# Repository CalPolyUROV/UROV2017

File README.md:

# UROV2017
The Git repository for UROV's 2016-2017 build year.

For the start of the year, everybody make their own folders for trying out sensor drivers. After you get your driver working, you can try your hand at adding it to the “main” program. Good luck!

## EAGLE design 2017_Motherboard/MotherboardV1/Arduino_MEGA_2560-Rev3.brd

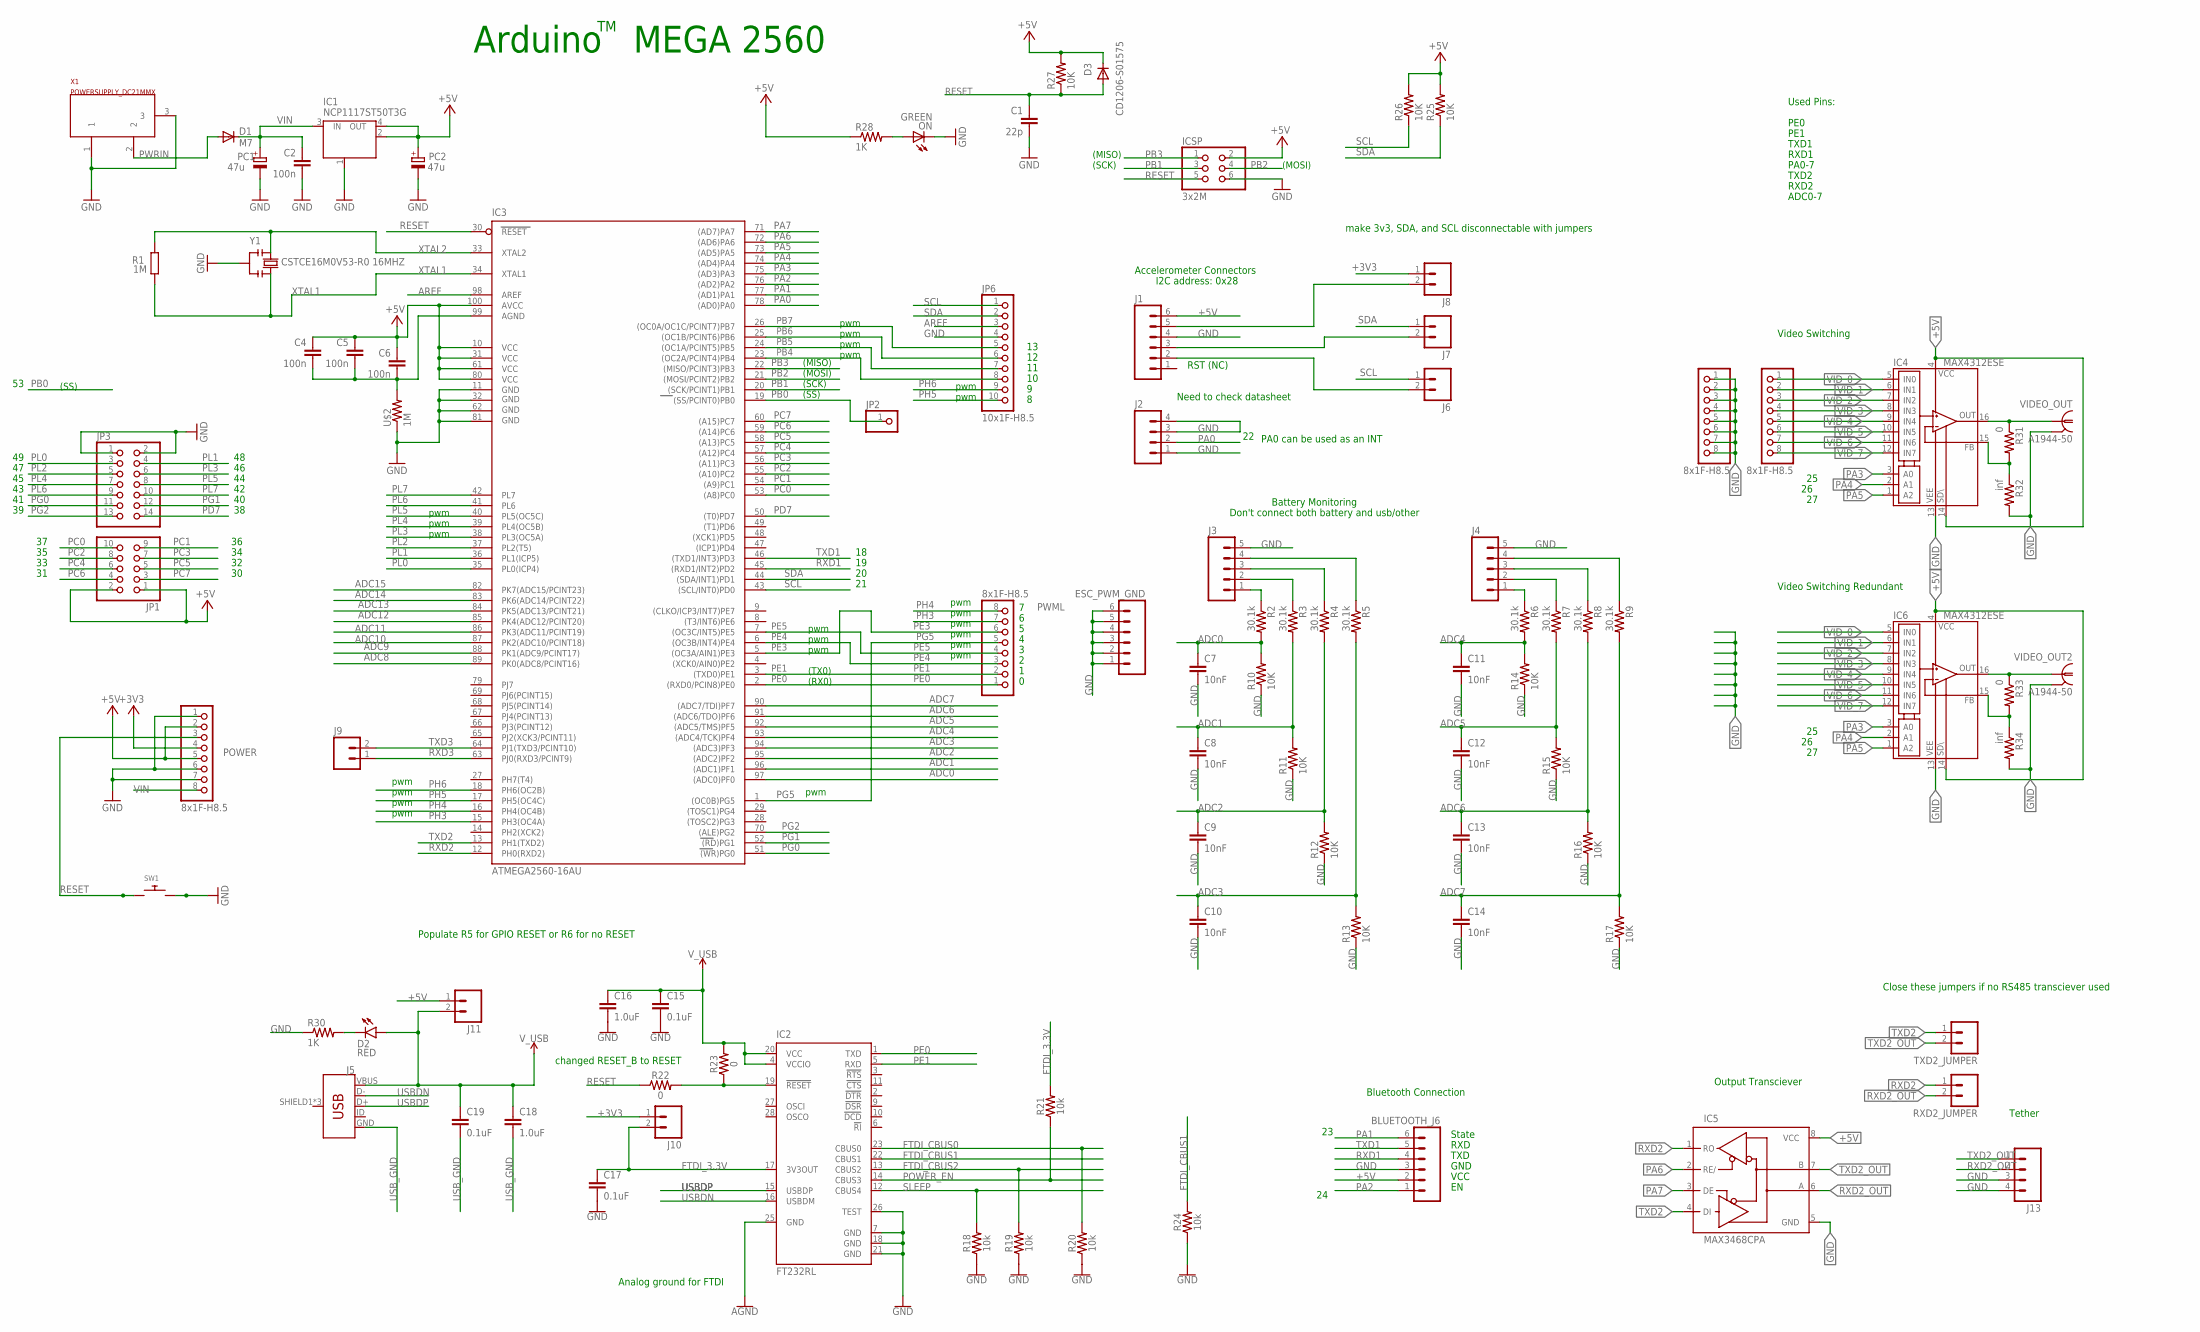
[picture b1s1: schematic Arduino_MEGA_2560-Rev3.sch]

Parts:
BLUETOOTH_J6: M06LONGPADS; 1X06_LONGPADS
C1: 22p; C0603-ROUND
C2, C4, C5, C6: 100n; C0603-ROUND
C7, C8, C9, C10, C11, C12, C13, C14: 10nF; 0603-CAP
C15, C17, C19: 0.1uF; 0603
C16, C18: 1.0uF; 0603
D1: M7; SMB
D2: RED; LED-0603
D3: CD1206-S01575; MINIMELF
ESC_PWM_GND: M06LONGPADS; 1X06_LONGPADS
IC1: NCP1117ST50T3G; SOT223
IC2: FT232RL; SSOP28
IC3: ATMEGA2560-16AU; TQFP100
IC4, IC6: MAX4312ESE; SO16
IC5: MAX3468CPA; DIL08
ICSP: 3x2M; 2X03
J1: M06LONGPADS; 1X06_LONGPADS
J2, J13: M04LONGPADS; 1X04_LONGPADS
J3, J4: M05JST-VERT; JST-5-PTH-VERT
J5: USB_MICRO-B_FEMALE-SMT; USB-B-MICRO-SMD
J6, J7, J8, J9, J10, J11: M02PTH; 1X02
JP1: PINHD-2X5; 2X05
JP2: PINHD-1X1; 1X01
JP3: PINHD-2X7; 2X07
JP6: 10x1F-H8.5; 1X10
ON: GREEN; CHIP-LED0805
PC1, PC2: 47u; PANASONIC_D
POWER: 8x1F-H8.5; 1X08
PWML: 8x1F-H8.5; 1X08
R1: 1M; R0603-ROUND
R2, R3, R4, R5, R6, R7, R8, R9: 30.1k; 0603-RES
R10, R11, R12, R13, R14, R15, R16, R17, R25, R26, R27: 10K; 0603-RES
R18, R19, R20, R21, R24: 10k; 0603
R22, R23: 0; 0603
R28, R30: 1K; 0603-RES
R31, R33: 0; 0603-RES
R32, R34: inf; 0603-RES
RXD2_JUMPER: M02PTH; 1X02
SW1: SWITCH_PUSHBUTTONC&K_KSS; BTN_CK_KSS
TXD2_JUMPER: M02PTH; 1X02
U$2: 1M; 0603-RES
VIDEO_IN: 8x1F-H8.5; 1X08
VIDEO_IN_GND: 8x1F-H8.5; 1X08
VIDEO_OUT, VIDEO_OUT2: A1944-50; A1944
X1: POWERSUPPLY_DC21MMX; POWERSUPPLY_DC-21MM
Y1: CSTCE16M0V53-R0 16MHZ; RESONATOR

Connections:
+3V3: J8.1, J10.1, POWER.4
+5V: BLUETOOTH_J6.2, C4.1, C5.1, C6.1, D3.C, IC1.2 (OUT), IC1.4 (OUT), IC3.10 (VCC), IC3.31 (VCC1), IC3.61 (VCC2), IC3.80 (VCC3), IC3.100 (AVCC), IC4.4 (V+), IC4.14 (!SHDN), IC5.8 (VCC), IC6.4 (V+), IC6.14 (!SHDN), ICSP.2, J1.6, J11.1, JP1.1, JP1.2, PC2.+, POWER.2, POWER.5, R25.2, R26.2, R27.2, R28.1
ADC0: C7.1, IC3.97 ((ADC0)PF0), R2.2, R10.2
ADC1: C8.1, IC3.96 ((ADC1)PF1), R3.2, R11.2
ADC2: C9.1, IC3.95 ((ADC2)PF2), R4.2, R12.2
ADC3: C10.1, IC3.94 ((ADC3)PF3), R5.2, R13.2
ADC4: C11.1, IC3.93 ((ADC4/TCK)PF4), R6.2, R14.2
ADC5: C12.1, IC3.92 ((ADC5/TMS)PF5), R7.2, R15.2
ADC6: C13.1, IC3.91 ((ADC6/TDO)PF6), R8.2, R16.2
ADC7: C14.1, IC3.90 ((ADC7/TDI)PF7), R9.2, R17.2
ADC8: IC3.89 (PK0(ADC8/PCINT16))
ADC9: IC3.88 (PK1(ADC9/PCINT17))
ADC10: IC3.87 (PK2(ADC10/PCINT18))
ADC11: IC3.86 (PK3(ADC11/PCINT19))
ADC12: IC3.85 (PK4(ADC12/PCINT20))
ADC13: IC3.84 (PK5(ADC13/PCINT21))
ADC14: IC3.83 (PK6(ADC14/PCINT22))
ADC15: IC3.82 (PK7(ADC15/PCINT23))
AGND: C4.2, C5.2, C6.2, IC2.25 (GND), IC3.99 (AGND), U$2.2
AREF: IC3.98 (AREF), JP6.3
FTDI_3.3V: C17.1, IC2.17 (3V3OUT), J10.2, R21.2
FTDI_CBUS0: IC2.23 (CBUS0), R20.2
FTDI_CBUS1: IC2.22 (CBUS1), R24.2
FTDI_CBUS2: IC2.13 (CBUS2), R19.2
GND: BLUETOOTH_J6.3, C1.2, C2.2, C7.2, C8.2, C9.2, C10.2, C11.2, C12.2, C13.2, C14.2, C15.2, C16.2, C17.2, ESC_PWM_GND.1, ESC_PWM_GND.2, ESC_PWM_GND.3, ESC_PWM_GND.4, ESC_PWM_GND.5, ESC_PWM_GND.6, IC1.1 (GND/ADJ), IC2.7 (GND), IC2.18 (GND), IC2.21 (GND), IC2.26 (TEST), IC3.11 (GND), IC3.32 (GND1), IC3.62 (GND2), IC3.81 (GND3), IC4.13 (V-), IC5.5 (GND), IC6.13 (V-), ICSP.6, J1.4, J2.1, J2.3, J2.4, J3.5, J4.5, J13.3, J13.4, JP3.1, JP3.2, JP6.4, ON.C, PC1.-, PC2.-, POWER.1, POWER.6, POWER.7, R10.1, R11.1, R12.1, R13.1, R14.1, R15.1, R16.1, R17.1, R18.1, R19.1, R20.1, R24.1, R30.1, R32.2, R34.2, SW1.P$2, U$2.1, VIDEO_IN_GND.1, VIDEO_IN_GND.2, VIDEO_IN_GND.3, VIDEO_IN_GND.4, VIDEO_IN_GND.5, VIDEO_IN_GND.6, VIDEO_IN_GND.7, VIDEO_IN_GND.8, VIDEO_OUT.2, VIDEO_OUT.3 (2), VIDEO_OUT.4 (2), VIDEO_OUT.5 (2), VIDEO_OUT2.2, VIDEO_OUT2.3 (2), VIDEO_OUT2.4 (2), VIDEO_OUT2.5 (2), X1.1, X1.3, Y1.2
unnamed: J3.1, R2.1
unnamed: ON.A, R28.2
unnamed: IC2.19 (!RESET), R22.2, R23.1
unnamed: J4.1, R6.1
unnamed: J3.2, R3.1
unnamed: J1.5, J8.2
unnamed: J3.3, R4.1
unnamed: J1.3, J7.2
unnamed: J3.4, R5.1
unnamed: J1.2, J6.2
unnamed: J4.2, R7.1
unnamed: J4.3, R8.1
unnamed: J4.4, R9.1
unnamed: D2.C, R30.2
unnamed: IC4.15 (FB), R31.2, R32.1
unnamed: IC6.15 (FB), R33.2, R34.1
PA0: IC3.78 ((AD0)PA0), J2.2
PA1: BLUETOOTH_J6.6, IC3.77 ((AD1)PA1)
PA2: BLUETOOTH_J6.1, IC3.76 ((AD2)PA2)
PA3: IC3.75 ((AD3)PA3), IC4.3 (A0), IC6.3 (A0)
PA4: IC3.74 ((AD4)PA4), IC4.2 (A1), IC6.2 (A1)
PA5: IC3.73 ((AD5)PA5), IC4.1 (A2), IC6.1 (A2)
PA6: IC3.72 ((AD6)PA6), IC5.2 (RE/)
PA7: IC3.71 ((AD7)PA7), IC5.3 (DE)
PB0: IC3.19 ((SS/PCINT0)PB0), JP2.1
PB1: IC3.20 ((SCK/PCINT1)PB1), ICSP.3
PB2: IC3.21 ((MOSI/PCINT2)PB2), ICSP.4
PB3: IC3.22 ((MISO/PCINT3)PB3), ICSP.1
PB4: IC3.23 ((OC2A/PCINT4)PB4), JP6.8
PB5: IC3.24 ((OC1A/PCINT5)PB5), JP6.7
PB6: IC3.25 ((OC1B/PCINT6)PB6), JP6.6
PB7: IC3.26 ((OC0A/OC1C/PCINT7)PB7), JP6.5
PC0: IC3.53 ((A8)PC0), JP1.10
PC1: IC3.54 ((A9)PC1), JP1.9
PC2: IC3.55 ((A10)PC2), JP1.8
PC3: IC3.56 ((A11)PC3), JP1.7
PC4: IC3.57 ((A12)PC4), JP1.6
PC5: IC3.58 ((A13)PC5), JP1.5
PC6: IC3.59 ((A14)PC6), JP1.4
PC7: IC3.60 ((A15)PC7), JP1.3
PD7: IC3.50 ((T0)PD7), JP3.14
PE0: IC2.1 (TXD), IC3.2 ((RXD0/PCIN8)PE0), PWML.1
PE1: IC2.5 (RXD), IC3.3 ((TXD0)PE1), PWML.2
PE3: IC3.5 ((OC3A/AIN1)PE3), PWML.6
PE4: IC3.6 ((OC3B/INT4)PE4), PWML.3
PE5: IC3.7 ((OC3C/INT5)PE5), PWML.4
PG0: IC3.51 ((WR)PG0), JP3.11
PG1: IC3.52 ((RD)PG1), JP3.12
PG2: IC3.70 ((ALE)PG2), JP3.13
PG5: IC3.1 ((OC0B)PG5), PWML.5
PH3: IC3.15 (PH3(OC4A)), PWML.7
PH4: IC3.16 (PH4(OC4B)), PWML.8
PH5: IC3.17 (PH5(OC4C)), JP6.10
PH6: IC3.18 (PH6(OC2B)), JP6.9
PL0: IC3.35 (PL0(ICP4)), JP3.3
PL1: IC3.36 (PL1(ICP5)), JP3.4
PL2: IC3.37 (PL2(T5)), JP3.5
PL3: IC3.38 (PL3(OC5A)), JP3.6
PL4: IC3.39 (PL4(OC5B)), JP3.7
PL5: IC3.40 (PL5(OC5C)), JP3.8
PL6: IC3.41 (PL6), JP3.9
PL7: IC3.42 (PL7), JP3.10
POWER_EN: IC2.14 (CBUS3), R21.1
PWRIN: D1.A, X1.2
RESET: C1.1, D3.A, IC3.30 (RESET), ICSP.5, POWER.3, R22.1, R27.1, SW1.P$1
RXD1: BLUETOOTH_J6.4, IC3.45 ((RXD1/INT2)PD2)
RXD2: IC3.12 (PH0(RXD2)), IC5.1 (RO), RXD2_JUMPER.1
RXD2_OUT: IC5.6 (A), J13.2, RXD2_JUMPER.2
RXD3: IC3.63 (PJ0(RXD3/PCINT9)), J9.1
SCL: IC3.43 ((SCL/INT0)PD0), J6.1, JP6.1, R26.1
SDA: IC3.44 ((SDA/INT1)PD1), J7.1, JP6.2, R25.1
SLEEP: IC2.12 (CBUS4), R18.2
TXD1: BLUETOOTH_J6.5, IC3.46 ((TXD1/INT3)PD3)
TXD2: IC3.13 (PH1(TXD2)), IC5.4 (DI), TXD2_JUMPER.1
TXD2_OUT: IC5.7 (B), J13.1, TXD2_JUMPER.2
TXD3: IC3.64 (PJ1(TXD3/PCINT10)), J9.2
USBDN: IC2.16 (USBDM), J5.D-
USBDP: IC2.15 (USBDP), J5.D+
USB_GND: C18.2, C19.2, J5.GND
VIDEO_OUT: IC4.16 (OUT), R31.1, VIDEO_OUT.1
VIDEO_OUT1: IC6.16 (OUT), R33.1, VIDEO_OUT2.1
VID_0: IC4.5 (IN0), IC6.5 (IN0), VIDEO_IN.1
VID_1: IC4.6 (IN1), IC6.6 (IN1), VIDEO_IN.2
VID_2: IC4.7 (IN2), IC6.7 (IN2), VIDEO_IN.3
VID_3: IC4.8 (IN3), IC6.8 (IN3), VIDEO_IN.4
VID_4: IC4.9 (IN4), IC6.9 (IN4), VIDEO_IN.5
VID_5: IC4.10 (IN5), IC6.10 (IN5), VIDEO_IN.6
VID_6: IC4.11 (IN6), IC6.11 (IN6), VIDEO_IN.7
VID_7: IC4.12 (IN7), IC6.12 (IN7), VIDEO_IN.8
VIN: C2.1, D1.C, IC1.3 (IN), PC1.+, POWER.8
V_USB: C15.1, C16.1, C18.1, C19.1, D2.A, IC2.4 (VCCIO), IC2.20 (VCC), J5.VBUS, J11.2, R23.2
XTAL1: IC3.34 (XTAL1), R1.1, Y1.3
XTAL2: IC3.33 (XTAL2), R1.2, Y1.1

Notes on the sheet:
Arduino MEGA 2560
(SCK)
(MISO)
(MOSI)
pwm
(TX0)
(RX0)
(SS)
Accelerometer Connectors
Battery Monitoring
Need to check datasheet
Don't connect both battery and usb/other
Populate R5 for GPIO RESET or R6 for no RESET
Analog ground for FTDI
make 3v3, SDA, and SCL disconnectable with jumpers
RST (NC)
PA0 can be used as an INT
I2C address: 0x28
Bluetooth Connection
State
RXD
TXD
GND
VCC
Used Pins:
PE0
PE1
TXD1
RXD1
PA0-7
ADC0-7
Tether
Video Switching
Output Transciever
Close these jumpers if no RS485 transciever used
changed RESET_B to RESET
TXD2
RXD2
Video Switching Redundant

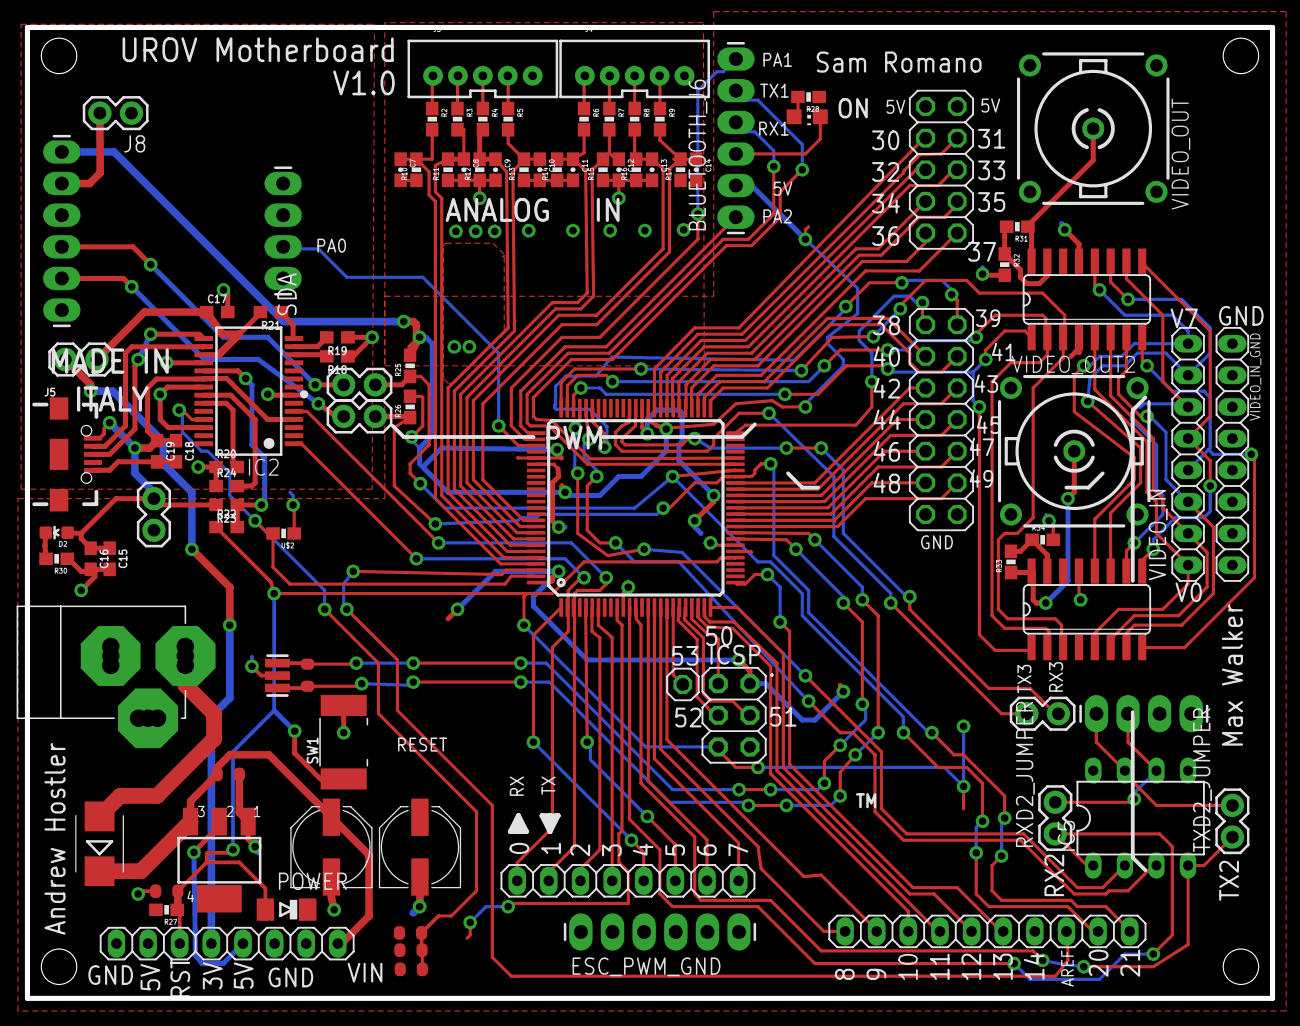
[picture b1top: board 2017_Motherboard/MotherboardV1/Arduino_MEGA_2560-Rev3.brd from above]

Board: 2 copper layers, 100.0 x 78.0 mm, 94 parts (0 on the bottom side), 110 nets.

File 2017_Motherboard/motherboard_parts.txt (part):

Partlist exported from /Users/maxwalker/Desktop/Folders/UROV2017/2017_Motherboard/Arduino_MEGA_2560-Rev3.sch at 3/4/17 11:43 AM

Qty Value                 Device                     Package             Parts                                                 Description                                                             MF MPN         OC_FARNELL OC_NEWARK PROD_ID    R35 VALUE
8                         M02PTH                     1X02                J6, J7, J8, J9, J10, J11, RXD2_JUMPER, TXD2_JUMPER    Standard 2-pin 0.1" header. Use with                                                                                            
2                         M04LONGPADS                1X04_LONGPADS       J2, J13                                               Header 4 CONN-09696                                                                                                              
2                         M05JST-VERT                JST-5-PTH-VERT      J3, J4                                                Header 5                                                                                                                        
3                         M06LONGPADS                1X06_LONGPADS       BLUETOOTH_J6, ESC_PWM_GND, J1                         Header 6                                                                                                                        
1                         PINHD-2X5                  2X05                JP1                                                   PIN HEADER                                                                                                                      
1                         PINHD-2X9                  2X09                JP2                                                   PIN HEADER                                                                                                                      
1                         RESISTOR0603-RES           0603-RES            R35                                                   1M Resistor                                                                                                                     
1                         USB_MICRO-B_FEMALE-SMT     USB-B-MICRO-SMD     J5                                                    USB Type Micro-B Connector                                                                                  
2   0                     0OHM-0603-1/10W-5%         0603                R22, R23                                              0Ω resistor                                                                                                 
2   0                     30.1KOHM1/10W1%(0603)      0603-RES            R31, R33                                              RES-08595                                                                                                   
3   0.1uF                 0.1UF-0603-25V-5%          0603                C15, C17, C19                                         0.1µF ceramic capacitors                                                                                    
2   1.0uF                 1.0UF-0603-16V-10%         0603                C16, C18                                              1µF ceramic capacitors                                                                                      
4   100n                  C-EU0603-RND               C0603-ROUND         C2, C4, C5, C6                                        CAPACITOR, European symbol                                                                                                      
11  10K                   10KOHM-1/10W-1%(0603)0603  0603-RES            R10, R11, R12, R13, R14, R15, R16, R17, R25, R26, R27 RES-00824                                                                                                   
5   10k                   10KOHM-0603-1/10W-1%       0603                R18, R19, R20, R21, R24                               10kΩ resistor                                                                                               
8   10nF                  10NF/10000PF-50V-10%(0603) 0603-CAP            C7, C8, C9, C10, C11, C12, C13, C14                   CAP-00867                                                                                                   
1   10x1F-H8.5            PINHD-1X10_ARD             1X10                JP6                                                   PIN HEADER                                                                                                                      
2   1K                    1KOHM-1/10W-1%(0603)       0603-RES            R28, R30                                              RES-07856                                                                                                   
1   1M                    R-EU_R0603                 R0603-ROUND         R1                                                    RESISTOR, European symbol                                                                                                       
1   22p                   C-EU0603-RND               C0603-ROUND         C1                                                    CAPACITOR, European symbol                                                                                                      
8   30.1k                 30.1KOHM1/10W1%(0603)      0603-RES            R2, R3, R4, R5, R6, R7, R8, R9                        RES-08595                                                                                                   
1   3x2M                  PINHD-2X3                  2X03                ICSP                                                  PIN HEADER                                                                                                                      
2   47u                   CPOL-EUD                   PANASONIC_D         PC1, PC2                                              POLARIZED CAPACITOR, European symbol                                                                                            
4   8x1F-H8.5             PINHD-1X8                  1X08                POWER, PWML, VIDEO_IN, VIDEO_IN_GND                   PIN HEADER                                                                                                                      
2   A1944-50              A1944-50                   A1944               VIDEO_OUT, VIDEO_OUT1                                 BNC CONNECTOR 50 Ohm                                                                                    
1   ATMEGA2560-16AU       ATMEGA25602560-16AU        TQFP100             IC3                                                   MICROCONTROLLER                                                                                                                 
1   CD1206-S01575         DIODE-MINIMELF             MINIMELF            D3                                                    DIODE                                                                                                                           
1   CSTCE16M0V53-R0 16MHZ RESONATORMU                RESONATOR           Y1                                                                                                                                                                                    
4   FIDUCIALMOUNT         FIDUCIALMOUNT              FIDUCIA-MOUNT       FD1, FD2, FD3, FD4                                                                                                                                                                    
1   FT232RL               FT232RL                    SSOP28              IC2                                                   Source: http://www.ftdichip.com/Documents/DataSheets/DS_FT232R_v104.pdf                        
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
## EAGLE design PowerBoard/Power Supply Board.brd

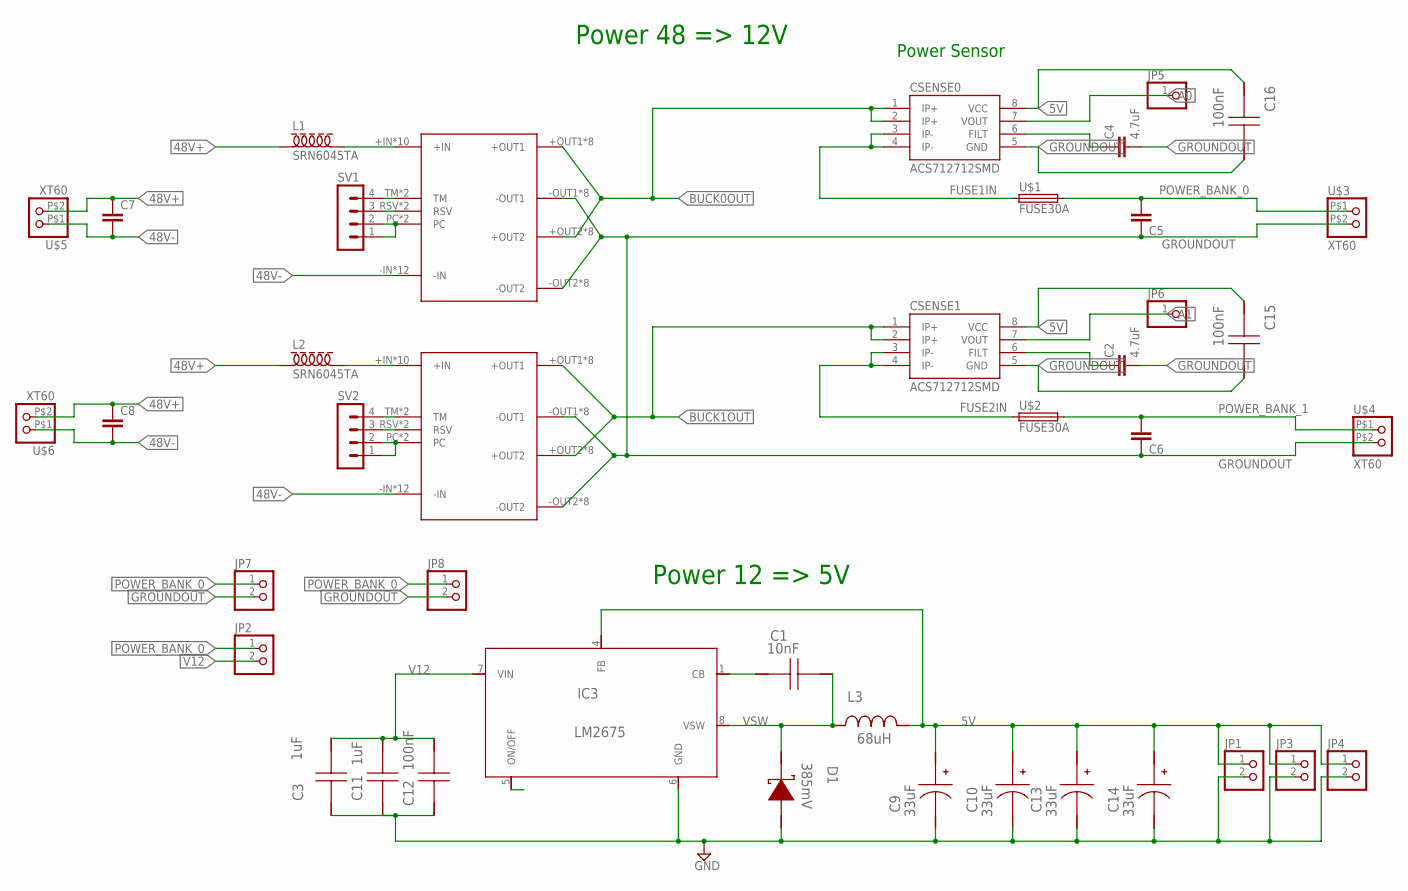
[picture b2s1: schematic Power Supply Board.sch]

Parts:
C1: 10nF; 0805
C2, C4: 4.7uF; 0603-CAP
C3, C11: 1uF; 0603
C5, C6, C7, C8: C2,5-3; C2.5-3
C9, C10, C13, C14: 33uF; CAPSMT_6_A09
C12, C15, C16: 100nF; 0805
CSENSE0, CSENSE1: ACS712712SMD; SO08
D1: 385mV; SOD-123
IC3: LM2675; M08A
JP1, JP2, JP3, JP4, JP7, JP8: PINHD-1X2; 1X02
JP5, JP6: PINHD-1X1; 1X01
L1, L2: SRN6045TA
L3: 68uH; SRU1028
SV1, SV2: MA04-1
U$1, U$2: FUSE30A
U$3, U$4, U$5, U$6: XT60
VC1, VC2: VOLTAGECONVERTER

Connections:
5V: C9.1 (+), C10.1 (+), C13.1 (+), C14.1 (+), C15.1, C16.1, CSENSE0.8 (VCC), CSENSE1.8 (VCC), IC3.4 (FB), JP1.1, JP3.1, JP4.1, L3.2
48V+: C7.1, C8.1, L1.P$1 (1), L2.P$1 (1), U$5.P$2 (2), U$6.P$2 (2)
48V-: C7.2, C8.2, U$5.P$1 (1), U$6.P$1 (1), VC1.-IN, VC1.-IN@0 (-IN), VC1.-IN@1 (-IN), VC1.-IN@2 (-IN), VC1.-IN@3 (-IN), VC1.-IN@4 (-IN), VC1.-IN@5 (-IN), VC1.-IN@6 (-IN), VC1.-IN@7 (-IN), VC1.-IN@8 (-IN), VC1.-IN@9 (-IN), VC1.-IN@10 (-IN), VC2.-IN, VC2.-IN@0 (-IN), VC2.-IN@1 (-IN), VC2.-IN@2 (-IN), VC2.-IN@3 (-IN), VC2.-IN@4 (-IN), VC2.-IN@5 (-IN), VC2.-IN@6 (-IN), VC2.-IN@7 (-IN), VC2.-IN@8 (-IN), VC2.-IN@9 (-IN), VC2.-IN@10 (-IN)
48VIN1: L1.P$2 (2), VC1.+IN, VC1.+IN@1 (+IN), VC1.+IN@2 (+IN), VC1.+IN@3 (+IN), VC1.+IN@4 (+IN), VC1.+IN@5 (+IN), VC1.+IN@6 (+IN), VC1.+IN@7 (+IN), VC1.+IN@8 (+IN), VC1.+IN@9 (+IN)
48VIN2: L2.P$2 (2), VC2.+IN, VC2.+IN@1 (+IN), VC2.+IN@2 (+IN), VC2.+IN@3 (+IN), VC2.+IN@4 (+IN), VC2.+IN@5 (+IN), VC2.+IN@6 (+IN), VC2.+IN@7 (+IN), VC2.+IN@8 (+IN), VC2.+IN@9 (+IN)
A0: CSENSE0.7 (VOUT), JP5.1
A1: CSENSE1.7 (VOUT), JP6.1
BUCK0OUT: CSENSE0.1 (IP+), CSENSE0.2 (IP+), VC1.+OUT1, VC1.+OUT1@1 (+OUT1), VC1.+OUT1@2 (+OUT1), VC1.+OUT1@3 (+OUT1), VC1.+OUT1@4 (+OUT1), VC1.+OUT1@5 (+OUT1), VC1.+OUT1@6 (+OUT1), VC1.+OUT1@7 (+OUT1), VC1.+OUT2, VC1.+OUT2@1 (+OUT2), VC1.+OUT2@2 (+OUT2), VC1.+OUT2@3 (+OUT2), VC1.+OUT2@4 (+OUT2), VC1.+OUT2@5 (+OUT2), VC1.+OUT2@6 (+OUT2), VC1.+OUT2@7 (+OUT2)
BUCK1OUT: CSENSE1.1 (IP+), CSENSE1.2 (IP+), VC2.+OUT1, VC2.+OUT1@1 (+OUT1), VC2.+OUT1@2 (+OUT1), VC2.+OUT1@3 (+OUT1), VC2.+OUT1@4 (+OUT1), VC2.+OUT1@5 (+OUT1), VC2.+OUT1@6 (+OUT1), VC2.+OUT1@7 (+OUT1), VC2.+OUT2, VC2.+OUT2@1 (+OUT2), VC2.+OUT2@2 (+OUT2), VC2.+OUT2@3 (+OUT2), VC2.+OUT2@4 (+OUT2), VC2.+OUT2@5 (+OUT2), VC2.+OUT2@6 (+OUT2), VC2.+OUT2@7 (+OUT2)
CB: C1.2, IC3.1 (CB)
FILT1: C4.1, CSENSE0.6 (FILT)
FILT2: C2.1, CSENSE1.6 (FILT)
FUSE1IN: CSENSE0.3 (IP-), CSENSE0.4 (IP-), U$1.P$1 (1), U$1.P$2 (1)
FUSE2IN: CSENSE1.3 (IP-), CSENSE1.4 (IP-), U$2.P$1 (1), U$2.P$2 (1)
GROUNDOUT: C2.2, C3.2, C4.2, C5.1, C6.1, C9.2 (-), C10.2 (-), C11.2, C12.2, C13.2 (-), C14.2 (-), C15.2, C16.2, CSENSE0.5 (GND), CSENSE1.5 (GND), D1.2 (A), IC3.6 (GND), JP1.2, JP3.2, JP4.2, JP7.2, JP8.2, U$3.P$2 (2), U$4.P$2 (2), VC1.-OUT1, VC1.-OUT1@1 (-OUT1), VC1.-OUT1@2 (-OUT1), VC1.-OUT1@3 (-OUT1), VC1.-OUT1@4 (-OUT1), VC1.-OUT1@5 (-OUT1), VC1.-OUT1@6 (-OUT1), VC1.-OUT1@7 (-OUT1), VC1.-OUT2, VC1.-OUT2@1 (-OUT2), VC1.-OUT2@2 (-OUT2), VC1.-OUT2@3 (-OUT2), VC1.-OUT2@4 (-OUT2), VC1.-OUT2@5 (-OUT2), VC1.-OUT2@6 (-OUT2), VC1.-OUT2@7 (-OUT2), VC2.-OUT1, VC2.-OUT1@1 (-OUT1), VC2.-OUT1@2 (-OUT1), VC2.-OUT1@3 (-OUT1), VC2.-OUT1@4 (-OUT1), VC2.-OUT1@5 (-OUT1), VC2.-OUT1@6 (-OUT1), VC2.-OUT1@7 (-OUT1), VC2.-OUT2, VC2.-OUT2@1 (-OUT2), VC2.-OUT2@2 (-OUT2), VC2.-OUT2@3 (-OUT2), VC2.-OUT2@4 (-OUT2), VC2.-OUT2@5 (-OUT2), VC2.-OUT2@6 (-OUT2), VC2.-OUT2@7 (-OUT2)
unnamed: SV1.3, VC1.RSV, VC1.RSV@1 (RSV)
unnamed: SV2.3, VC2.RSV, VC2.RSV@1 (RSV)
PC1: SV1.1, SV1.2, SV2.1, SV2.2, VC1.PC, VC1.PC21 (PC), VC2.PC, VC2.PC21 (PC)
POWER_BANK_0: C5.2, JP2.1, JP7.1, JP8.1, U$1.P$3 (2), U$1.P$4 (2), U$3.P$1 (1)
POWER_BANK_1: C6.2, U$2.P$3 (2), U$2.P$4 (2), U$4.P$1 (1)
TM1: SV1.4, VC1.TM, VC1.TM@1 (TM)
TM2: SV2.4, VC2.TM, VC2.TM@1 (TM)
V12: C3.1, C11.1, C12.1, IC3.7 (VIN), JP2.2
VSW: C1.1, D1.1 (K), IC3.8 (VSW), L3.1

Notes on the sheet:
Power 12 => 5V
Power 48 => 12V
Power Sensor

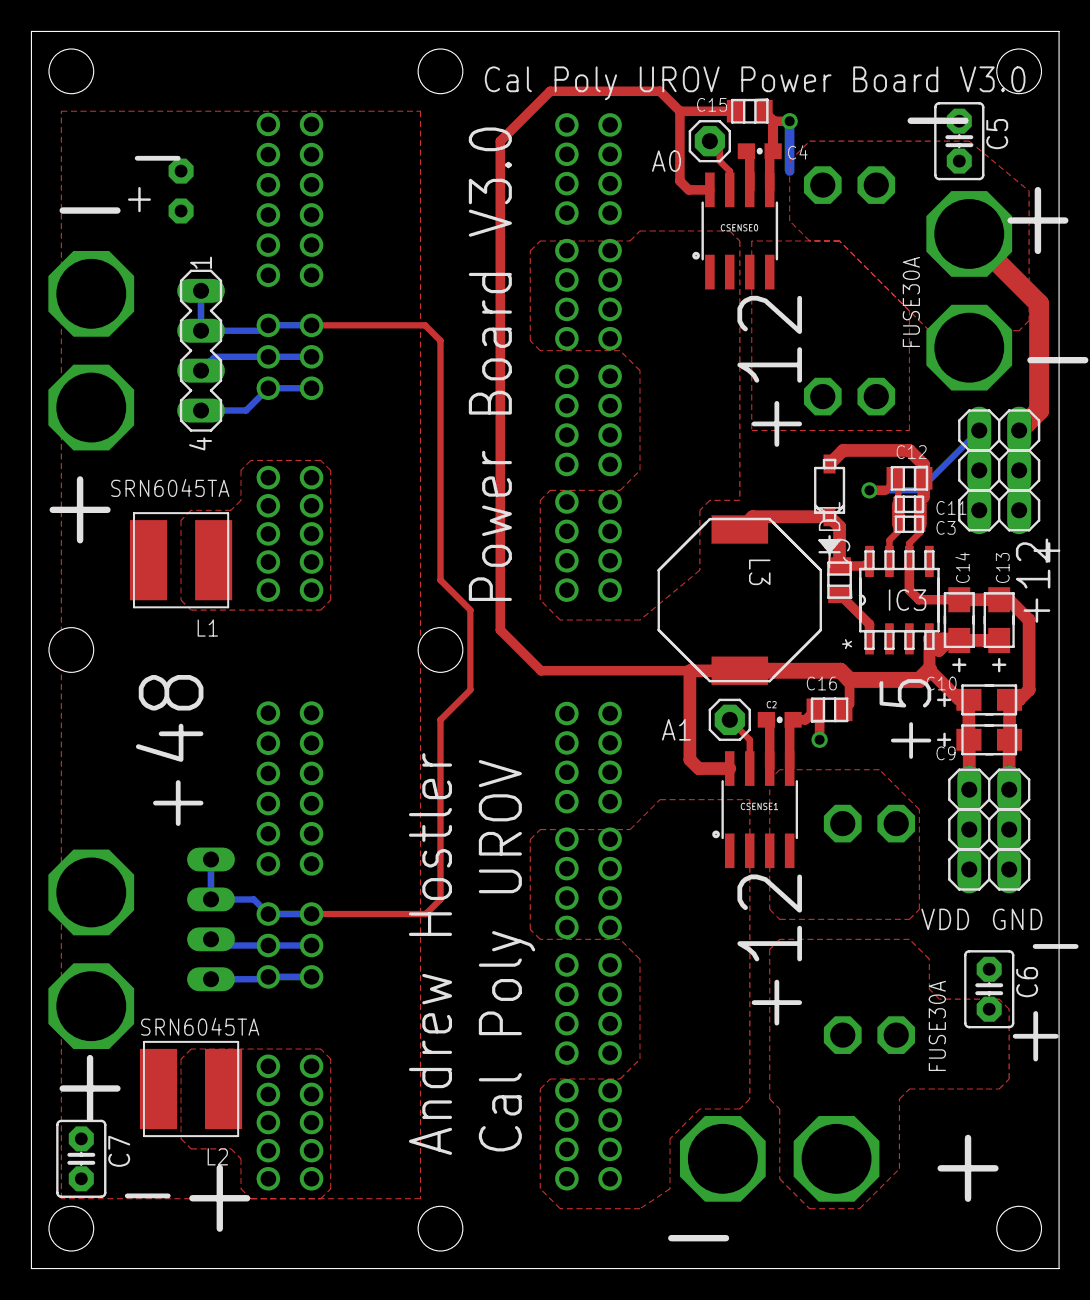
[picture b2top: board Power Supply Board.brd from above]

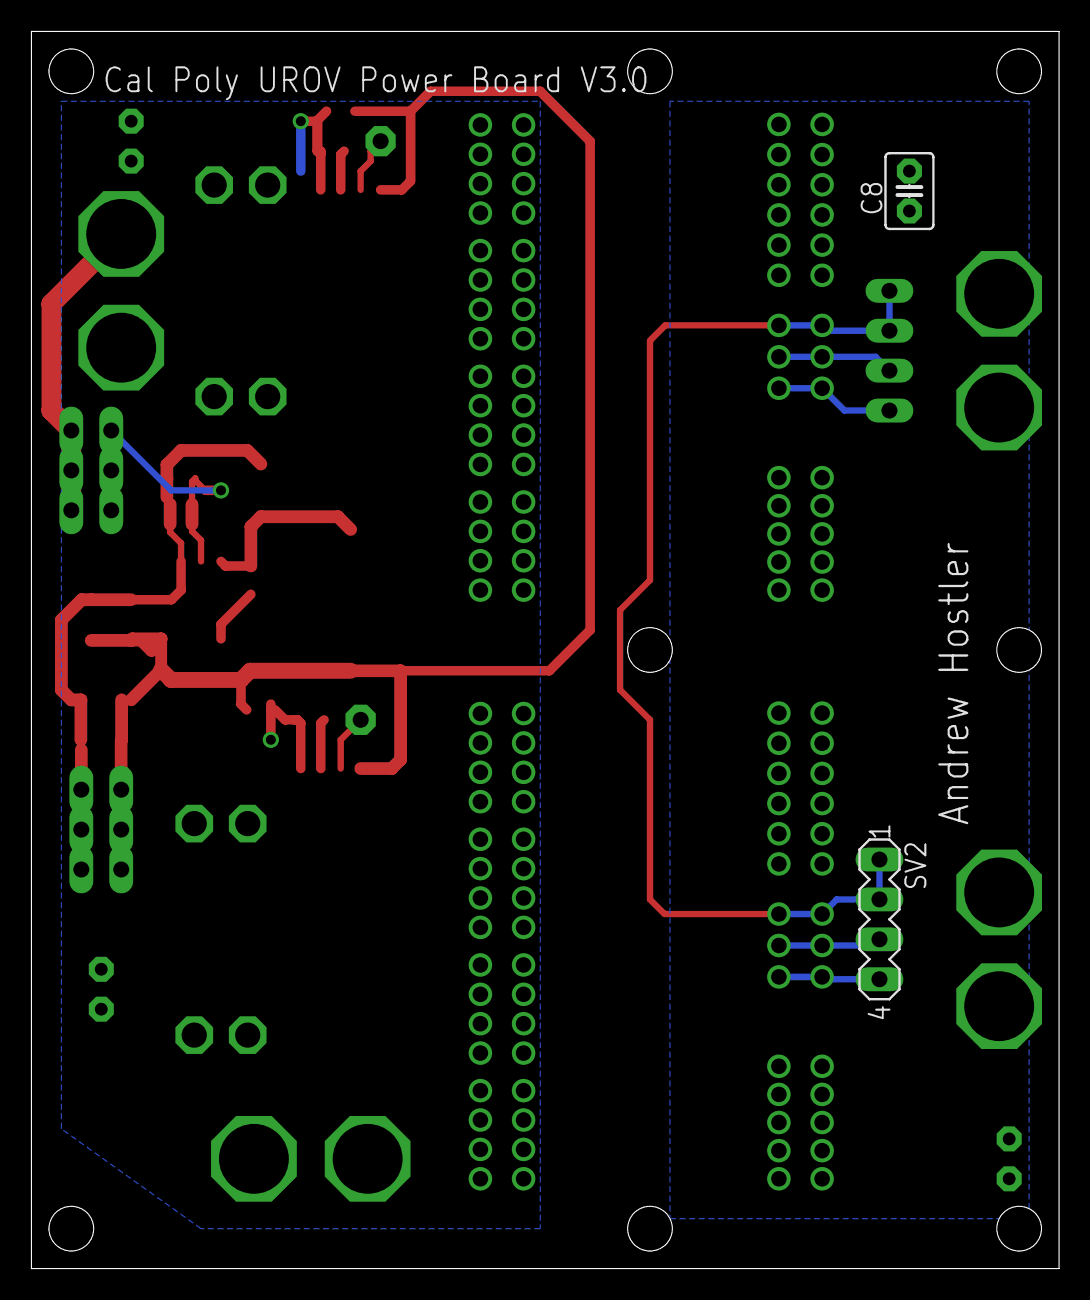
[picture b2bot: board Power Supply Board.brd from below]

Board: 2 copper layers, 65.4 x 78.7 mm, 41 parts (5 on the bottom side), 24 nets.

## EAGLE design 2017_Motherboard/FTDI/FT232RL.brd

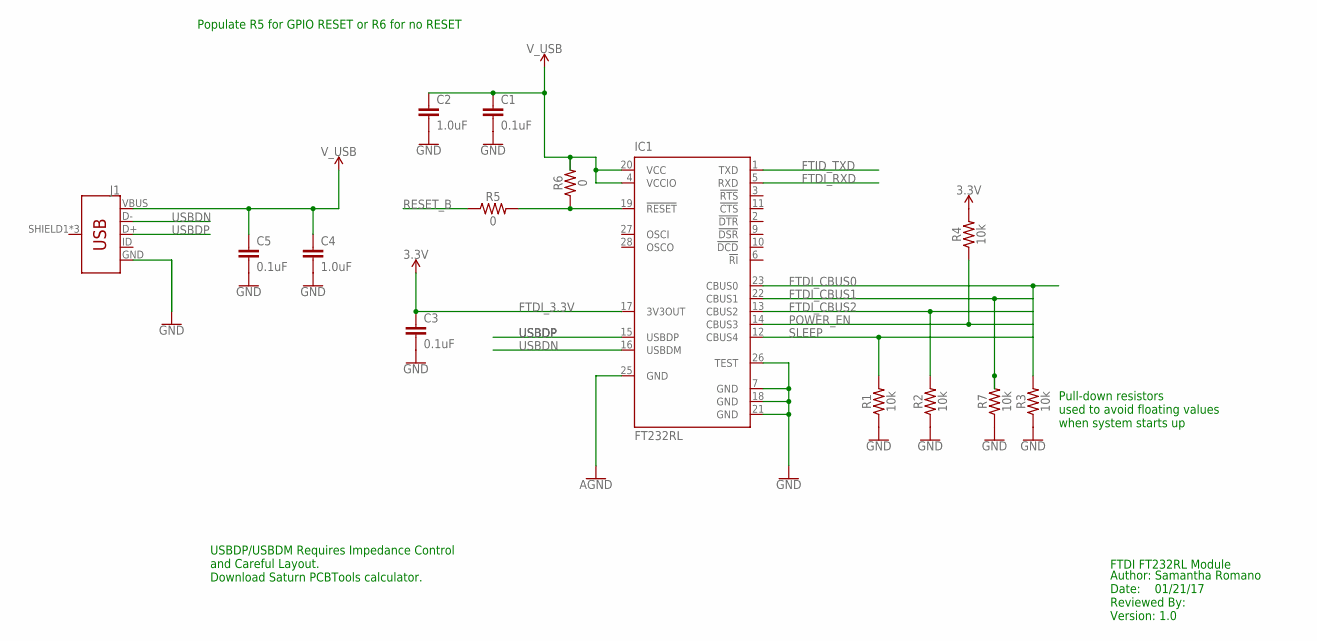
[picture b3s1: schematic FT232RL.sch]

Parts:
C1, C3, C5: 0.1uF; 0603
C2, C4: 1.0uF; 0603
IC1: FT232RL; SSOP28
J1: USB_MICRO-B_FEMALE-SMT; USB-B-MICRO-SMD
R1, R2, R3, R4, R7: 10k; 0603
R5, R6: 0; 0603

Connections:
3.3V: R4.2
AGND: IC1.25 (GND)
FTDI_3.3V: C3.1, IC1.17 (3V3OUT)
FTDI_CBUS0: IC1.23 (CBUS0), R3.2
FTDI_CBUS1: IC1.22 (CBUS1), R7.2
FTDI_CBUS2: IC1.13 (CBUS2), R2.2
FTDI_RXD: IC1.5 (RXD)
FTID_TXD: IC1.1 (TXD)
GND: C1.2, C2.2, C3.2, C4.2, C5.2, IC1.7 (GND), IC1.18 (GND), IC1.21 (GND), IC1.26 (TEST), R1.1, R2.1, R3.1, R7.1
unnamed: IC1.19 (!RESET), R5.2, R6.1
POWER_EN: IC1.14 (CBUS3), R4.1
RESET_B: R5.1
SLEEP: IC1.12 (CBUS4), R1.2
USBDN: IC1.16 (USBDM), J1.D-
USBDP: IC1.15 (USBDP), J1.D+
USB_GND: J1.GND
V_USB: C1.1, C2.1, C4.1, C5.1, IC1.4 (VCCIO), IC1.20 (VCC), J1.VBUS

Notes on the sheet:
USBDP/USBDM Requires Impedance Control and Careful Layout. Download Saturn PCBTools calculator.
Pull-down resistors used to avoid floating values when system starts up
FTDI FT232RL Module
Author: Samantha Romano Date: 01/21/17 Reviewed By: Version: 1.0
Populate R5 for GPIO RESET or R6 for no RESET

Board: 2 copper layers, 14 parts (0 on the bottom side), 11 nets, no tracks yet.

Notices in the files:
parts and their libraries:
SparkFun-Connectors: Licensing: Creative Commons ShareAlike 4.0 International - https://creativecommons.org/licenses/by-sa/4.0
